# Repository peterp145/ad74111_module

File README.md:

# ad74111_module
AD4111 audio codec IC and supporting hardware with PMOD connector.

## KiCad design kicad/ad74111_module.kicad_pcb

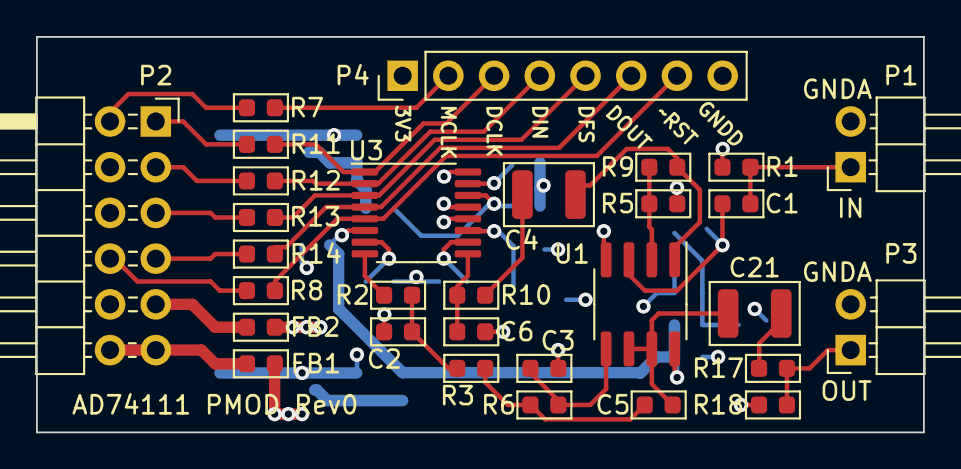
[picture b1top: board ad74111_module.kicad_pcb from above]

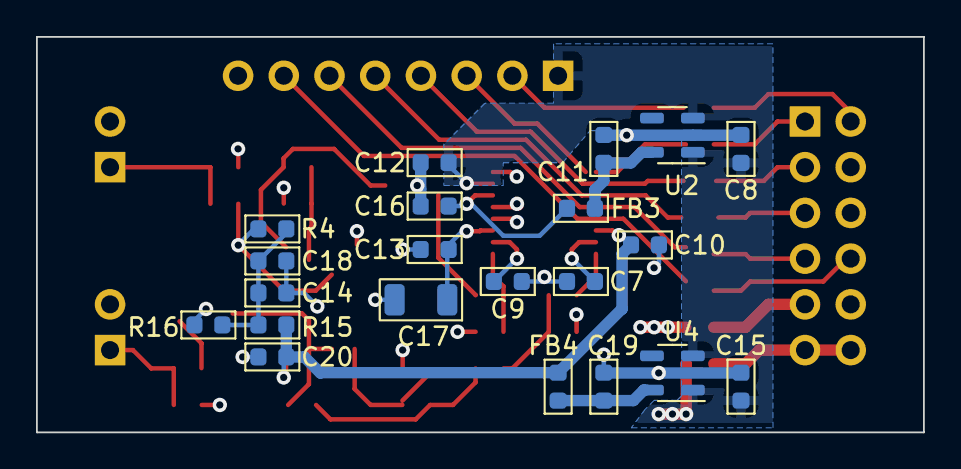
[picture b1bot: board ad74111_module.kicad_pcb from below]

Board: 4 copper layers, 49.3 x 22.0 mm, 51 parts (21 on the bottom side), 37 nets.

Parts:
C1, C10, C12, C13, C16, C18, C20: cap_0.1UF_5%_50V_0603_X7R; C_0603_1608Metric
C2: cap_2200PF_2%_50V_0603_C0G-NP0; C_0603_1608Metric
C3, C5, C7, C9: cap_1000PF_1%_50V_0603_C0G-NP0; C_0603_1608Metric
C4, C21: cap_47UF_10%_16V_1210_X6S; C_1210_3225Metric
C6: cap_10000PF_50V_0603_C0G-NP0; C_0603_1608Metric
C8, C11, C14, C15, C19: cap_1UF_10%_16V_0603_X7R; C_0603_1608Metric
C17: cap_10UF_10%_16V_1206_X7R; C_1206_3216Metric
FB1, FB2, FB3, FB4: bead_600R_100MHz; R_0603_1608Metric
P1, P3: Conn_01x02_100mil_right_angle_male
P2: Conn_02x06_100mil_right_angle_male
P4: Conn_01x08; Conn_01x08_100mil_male
R1, R4: res_2M2_1%_0.1W_0603; R_0603_1608Metric
R2: res_820R_1%_0.1W_0603; R_0603_1608Metric
R3, R6: res_8K2_1%_0.1W_0603; R_0603_1608Metric
R5, R9: res_0R_0603; R_0603_1608Metric
R7, R8, R11, R12, R13, R14: res_33R_5%_0.1W_0603; R_0603_1608Metric
R10: res_51R_1%_0.1W_0603; R_0603_1608Metric
R15, R16: res_100K_1%_0.1W_0603; R_0603_1608Metric
R17: res_100R_1%_0.1W_0603; R_0603_1608Metric
R18: res_10K_1%_0.1W_0603; R_0603_1608Metric
U1: LMV722; SOIC-8_3.9x4.9mm_P1.27mm
U2, U4: LP5951MG-2.5; SOT-23-5
U3: AD74111; TSSOP-16_4.4x5mm_P0.65mm

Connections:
+2V5: C16.1, FB3.1, U3.14 (DVDD2)
+3V3: C8.1, C12.1, C15.1, FB1.1, P4.1, U2.1 (IN), U2.3 (EN), U3.15 (DVDD1), U4.1 (IN), U4.3 (EN)
/3v3_in: FB1.2, P2.6, P2.12
/audio_in: C1.1, P1.1, R1.1
/audio_out: P3.1, R17.2, R18.1
/dclk: P4.3, R11.2, U3.1 (DCLK)
/dfs: P4.5, R13.2, U3.3 (DFS)
/din: P4.4, R12.2, U3.2 (DIN)
/dout: P4.6, R14.2, U3.4 (DOUT)
/mclk: P4.2, R7.1, U3.16 (MCLK)
/vbias: C14.1, C18.1, R4.1, R15.2, R16.1
/vin: C6.1, R10.2, U3.9 (VIN)
/vout: R2.1, U3.8 (VOUT)
/~reset: P4.7, R8.1, U3.5 (~RESET)
GNDA: C2.2, C3.2, C6.2, C7.2, C9.2, C10.2, C13.2, C14.2, C15.2, C17.2, C18.2, C19.2, C20.2, FB2.1, P1.2, P3.2, R1.2, R5.1, R16.2, R18.2, U1.4 (V-), U3.12 (AGND), U4.2 (GND)
GNDD: C8.2, C11.2, C12.2, C16.2, FB2.2, P2.5, P2.11, P4.8, U2.2 (GND), U3.13 (DGND)
unnamed: C1.2, R4.2, U1.3 (+)
unnamed: C2.1, R2.2, R3.1
unnamed: C3.1, R6.2, U1.5 (+)
unnamed: C4.1, R10.1
unnamed: C4.2, R9.2, U1.1
unnamed: C5.1, R3.2, R6.1
unnamed: C7.1, U3.7 (CAPN)
unnamed: C9.1, U3.10 (CAPP)
unnamed: C11.1, FB3.2, U2.5 (OUT)
unnamed: C13.1, C17.1, U3.11 (REFCAP)
unnamed: C19.1, FB4.2, U4.5 (OUT)
unnamed: C21.1, R17.1
unnamed: C5.2, C21.2, U1.6 (-), U1.7
unnamed: P2.1, R11.1
unnamed: P2.2, R12.1
unnamed: P2.3, R13.1
unnamed: P2.4, R14.1
unnamed: P2.7, R7.2
unnamed: P2.10, R8.2
unnamed: R5.2, R9.1, U1.2 (-)
VAA: C10.1, C20.1, FB4.1, R15.1, U1.8 (V+), U3.6 (AVDD)

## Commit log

2021-12-13 created kicad project
2021-12-13 AD74111 datasheets
2021-12-31 created project and started schematic
2022-01-11 rev0 gerb files
2022-01-15 rev0 release
2022-01-15 started python demo app
